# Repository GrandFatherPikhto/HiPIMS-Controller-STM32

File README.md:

# HiPiMS-Controller-STM32-v099

Плата управления HiPIMS: STM32F103C8 (U4) + Cyclone 10 LP 10CL006YE144 (IC1) с конфигурационным флешем
W25Q128JVS (U5).

Обозначения в этом файле — по схеме после переаннотации 16.11.2026.

## Что делает плата

* FPGA формирует сигналы управления: два силовых канала HP (по два плеча A/B, разъёмы J10/J11) и 12 логических
  каналов CH (J8/J9).
* STM32 — интерфейс оператора (LCD 1602 по I²C, энкодер с кнопкой), UART наружу и обмен с FPGA по SPI1.
* Все выходы и входы FPGA к разъёмам проходят через 74HC14 (U6–U13, питание 3.3 В). Каждый сигнал проходит два
  инвертора подряд, то есть уровень не инвертируется.

## Плата

* 4 слоя, 1.6 мм, около 115 × 94 мм.
* Зона GND_ALL на всех четырёх слоях, отдельных земель нет.
* Четыре крепёжных отверстия M3 (Ø 3.2 мм), межосевое 100.43 × 76.32 мм.

## Питание

Вход — **+5 В на J1** (JST VH, 1 = +5 В, 2 = GND). Защиты от переполюсовки нет: разъём полярный.

```text
J1 +5V_DIRTY ─ C9 100 мкФ ─ FB4 ─ +5V ─┬─ U2 AMS1117-3.3 ─ +3V3_DIRTY ─ FB1 ─ +3V3 ─┬─ FB10 ─ VCCIO FPGA
                                       │                                           ├─ FB6 ─ VDD MCU
                                       │                                           ├─ FB5 ─ VDDA MCU
                                       │                                           ├─ R26 2.2 Ом ─ флеш U5
                                       │                                           └─ R19 2.2 Ом ─ генератор Y3
                                       ├─ U1 AMS1117-1.2 ─ +1V2_DIRTY ─ FB2 ─ +1V2 ─┬─ FB7 ─ VCCINT
                                       │                                           └─ FB8 ─ VCCD_PLL
                                       ├─ U3 LM317 (R3 = R4 = 240 Ом) ─ +2V5_DIRTY ─ FB3 ─ +2V5 ─ FB9 ─ VCCA
                                       ├─ J5 (LCD), J6 (энкодер)
                                       └─ светодиод D6
```

* На входе AMS1117 — 10 мкФ + 100 нФ у вывода 3 (U1: C2/C6, U2: C1/C5).
* На выходе AMS1117 — тантал 47 мкФ (C3, C4); он даёт ESR, нужный для их устойчивости.
* У LM317 стоят D3 (выход → вход) и D4 (ADJ → выход) — штатная защита при разряде конденсаторов.
* Светодиоды питания: D6 синий (+5V), D1 зелёный (+3V3), D5 оранжевый (+2V5), D2 белый (+1V2) — про D2 см.
  «На проверку».

## Разъёмы

| Разъём | Тип | Назначение |
| --- | --- | --- |
| J1 | JST VH 2P | вход +5 В |
| J2 | штырь 1×2 | перемычка BOOT0 (STM32) |
| J3 | штырь 1×5 | SWD (STM32) |
| J4 | JST XH 4P | UART: 1 GND, 2 TX, 3 GND, 4 RX (через 330 Ом) |
| J5 | JST XH 4P | LCD 1602 (I²C): 1 GND, 2 +5V, 3 SDA (PB7), 4 SCL (PB6) |
| J6 | JST XH 5P | энкодер: 1 +5V, 2 A (PA0), 3 B (PA1), 4 кнопка (PA2), 5 GND |
| J7 | IDC 2×5 | JTAG FPGA (USB-Blaster) |
| J8 | IDC 2×6 | CH_OUT 0–5 на чётных выводах, нечётные — GND |
| J9 | IDC 2×6 | CH_OUT 6–11 на чётных выводах, нечётные — GND |
| J10 | IDC 2×6 | HP-канал 0 (плечи A/B) |
| J11 | IDC 2×6 | HP-канал 1 (плечи A/B) |

### HP-каналы (J10, J11)

| Вывод | Сигнал |
| --- | --- |
| 2 / 8 | CTL плеча A / B (выход) |
| 4 / 10 | RST плеча A / B (выход) |
| 6 / 12 | FLT плеча A / B (вход) |
| нечётные | GND |

* Стыкуются кабелем IDC 2×6 с J1 платы **HP-ISO-Channel-v099** (гальваническая развязка, дальше 5-вольтовая
  логика на HP-Channel / HP-Power). Логика на этом разъёме — 3.3 В.
* **CTL и RST** подтянуты к GND (2.2 кОм на входе 74HC14). Пока FPGA не сконфигурирована, на выходах «0»:
  ключ закрыт, драйвер в сбросе.
* **FLT** подтянут к GND (10 кОм, R48–R51). «0» = авария; снятый кабель тоже читается как авария. Это совпадает с
  fail-safe low у ISO7720F на HP-ISO-Channel.

### CH-каналы (J8, J9)

Двенадцать выходов FPGA через 74HC14. На входах буферов подтяжки 2.2 кОм к GND, поэтому во время конфигурации
FPGA на выходах «0».

## STM32 (U4)

* Кварцы: Y2 8 МГц (HSE, 12 пФ), Y1 32.768 кГц (LSE, 6.8 пФ).
* SPI1 к FPGA: PA4 CS_N (подтяжка 10 кОм вверх), PA5 SCK, PA6 MISO, PA7 MOSI; PB0 — IRQ от FPGA.
* I²C (LCD): PB6 SCL, PB7 SDA. Выводы 5-вольтовые (FT), подтяжки модуля LCD к +5 В допустимы.
* Энкодер: PA0, PA1, PA2. Подтяжек на плате нет — нужны внутренние подтяжки МК или подтяжки на модуле энкодера.
  См. «На проверку».
* Кнопка сброса SW1 (через 100 Ом на NRST).

## FPGA (IC1)

* Тактовая частота — генератор Y3 (корпус 3225), выход через 33 Ом. Вывод ST подтянут к питанию (1 кОм),
  питание генератора через 2.2 Ом.
* Конфигурация с флеша U5 — см. «Прошивка».

## На проверку

1. **D2 (белый, +1V2) не загорится.** Прямое напряжение белого светодиода около 3 В, а шина 1.2 В. Даже красному
   (≈1.8 В) не хватит. Если индикатор 1.2 В нужен — питать светодиод от +3V3 через транзистор, ключом от +1V2;
   иначе убрать D2 и R2.
2. **Энкодер на J6 — принято как есть.** Модуль энкодера с подтяжками питается +5 В, сигналы идут на PA0–PA2,
   которые у STM32F103 не 5-вольтовые (не FT). Ток через защитные диоды около 0.1–0.2 мА (10 кОм к 5 В), такая
   связка на практике работает. Строго по даташиту это выход за диапазон входа. Если когда-нибудь понадобится
   чисто — питать J6.1 от +3V3 или перенести сигналы на FT-выводы (PB…).
3. **Y3: значение в схеме — SG-7050CAN** (корпус 7.0 × 5.0 мм), а стоит генератор 3225. Исправить Value и
   Datasheet на реальный партномер, чтобы в BOM не ушёл чужой корпус. Предупреждение о фильтре футпринта после
   этого можно игнорировать.
4. **TCK подтянут 4.7 кОм** (R15), Intel советует 1 кОм — если JTAG сбоит.
5. **Площадка CL_NCONFIG** для прошивки флеша клипсой — при следующей доработке (см. «Прошивка»).
6. **На первой плате** осциллографом: +5V у входа AMS1117 и их выходы при включении и при подключении горячего
   источника. Затухающий выброс на 1–2 периода — норма. Долгий звон лечится резистором 0.5–1 Ом последовательно
   с одним из 10 мкФ.

## Прошивка

### STM32 (U4)

Основной путь — **SWD, разъём J3**:

| J3 | Цепь |
| --- | --- |
| 1 | +3V3 |
| 2 | SWDIO (PA13) |
| 3 | SWCLK (PA14) |
| 4 | NRST |
| 5 | GND |

* NRST выведен на разъём → можно подключаться с удержанием сброса (connect under reset), даже если прошивка
  отключила SWD.
* Если плата питается сама, вывод 3.3V программатора на J3.1 не подключать (у клонов ST-Link это выход). Хватает
  GND, SWDIO, SWCLK, NRST.

Запасной путь — **системный загрузчик по UART, разъём J4** (1 GND, 2 TX, 3 GND, 4 RX; линии через 330 Ом):

* BOOT0 подтянут к GND (R7 10 кОм), перемычка **J2** подаёт на него VDD. BOOT1 (PB2) — 10 кОм на GND.
* Перемычка J2 снята → старт из флеша; установлена → старт из системного загрузчика.

### FPGA: загрузка .sof по JTAG (без флеша)

Разъём **J7**, распиновка USB-Blaster: 1 TCK, 2 GND, 3 TDO, 4 VCC (+3V3), 5 TMS, 9 TDI, 10 GND (6–8 не
подключены). Загрузка в саму FPGA, флеш не участвует; пропадает при снятии питания.

TCK подтянут к GND 4.7 кОм (R15). Intel рекомендует 1 кОм; если JTAG сбоит на длинном кабеле — поменять R15
на 1 кОм.

### FPGA: конфигурация с флеша

Схема конфигурации — **AS ×1, стандартный POR, 3.3 В**: MSEL[2:0] = 010 (MSEL1 на VCCA, MSEL0/MSEL2 на GND),
nCE на GND, nCONFIG/nSTATUS/CONF_DONE подтянуты 10 кОм к +3V3_VCCIO. Шина AS напрямую к U5; WP и HOLD флеша
в «1».

**Флеш — Winbond, а не Intel EPCS/EPCQ.** Последствия:

1. **Галка Disable EPCS/EPCQ ID check — обязательна.** File → Convert Programming Files → **Advanced…** →
   **Disable EPCS/EPCQ ID check**. Галка записывается в сам файл прошивки и выключает проверку ID, которую
   **FPGA делает при загрузке с флеша**. Без неё Cyclone может не загрузиться с W25Q даже при правильно
   записанных данных. Ставить при генерации **и .jic, и .rpd**.
   Для `quartus_cpf` из командной строки то же самое — строка `PGMIO_IGNORE_EPCS_ID_CHECK=1` в `quartus.ini`.
2. **Целевое устройство при генерации — EPCQ128A** (или EPCS128): W25Q128JV в списке Quartus нет.
3. **Запись .jic через JTAG (J7).** Галка из п. 1 **не** отключает проверку ID, которую делает сам Quartus
   Programmer при записи. По отчётам W25Q128JV под EPCQ128A записывается, но это проверить на первой плате.

Проверка на первой плате:

1. Сгенерировать .jic под EPCQ128A с галкой из п. 1.
2. Записать через JTAG.
3. Снять и вернуть питание.
4. Убедиться, что CONF_DONE поднялся.

### FPGA: запасной путь — флеш напрямую клипсой

Если Quartus Programmer не возьмёт флеш, U5 пишется внешним SPI-программатором.

* **Клипса SOIC-8 208 mil** прямо на U5 (корпус 5.3 мм).
* **FPGA держать в сбросе:** CL_NCONFIG в «0» на всё время записи, тогда FPGA не выходит на шину AS. Отдельной
  площадки сейчас нет — только подтяжка R22. При доработке платы стоит добавить площадку CL_NCONFIG рядом с GND.
  (Поведение шины AS при nCONFIG = 0 и nCE = GND — сверить с Cyclone 10 LP Handbook, раздел AS-программирования.)
* **Питание — от платы**, VCC программатора не подключать: иначе через R26 (2.2 Ом) он кормит всю шину +3V3
  вместе с FPGA.
* **Логика программатора — 3.3 В.** Дешёвый CH341A «из коробки» даёт 5 В на SPI — нужна доработка на 3.3 В или
  другой программатор (FT2232H, Raspberry Pi, Bus Pirate).
* **Файл — .rpd**, а не .jic: Convert Programming Files, EPCQ128A, Active Serial, **с галкой Disable EPCS/EPCQ ID
  check**. Писать с адреса 0 (flashrom, ch341prog). В .rpd биты уже в порядке AS.
* После записи отпустить CL_NCONFIG или передёрнуть питание → CONF_DONE должен подняться.

### Источники

* [Cyclone 10 LP Handbook — MSEL Pin Settings](https://www.intel.com/content/www/us/en/docs/programmable/683777/current/msel-pin-settings.html)
* [AN 1013: Using Generic QSPI Flash — Disable Flash ID Check](https://www.intel.com/content/www/us/en/docs/programmable/855235/current/disable-flash-id-check.html)
* [Intel KB: When should the "Disable EPCS/EPCQ ID check" option be enabled](https://community.altera.com/kb/knowledge-base/when-should-the-%C2%93disable-epcsepcq-id-check%C2%94-option-be-enabled-in-the-convert-pro/340830)
* [Intel forum — W25Q128JVSIQ: which flash for .jic](https://community.altera.com/discussions/fpga-device/w25q128jvsiq-which-flash-for-jic-file/337276)
* [Intel forum — Cyclone 10 LP boot issue with W25Q128JVSIM](https://community.altera.com/discussions/quartus-prime/cyclone-10-lp-boot-up-issue-for-winbond-flash-w25q128jvsim-tr/313210)

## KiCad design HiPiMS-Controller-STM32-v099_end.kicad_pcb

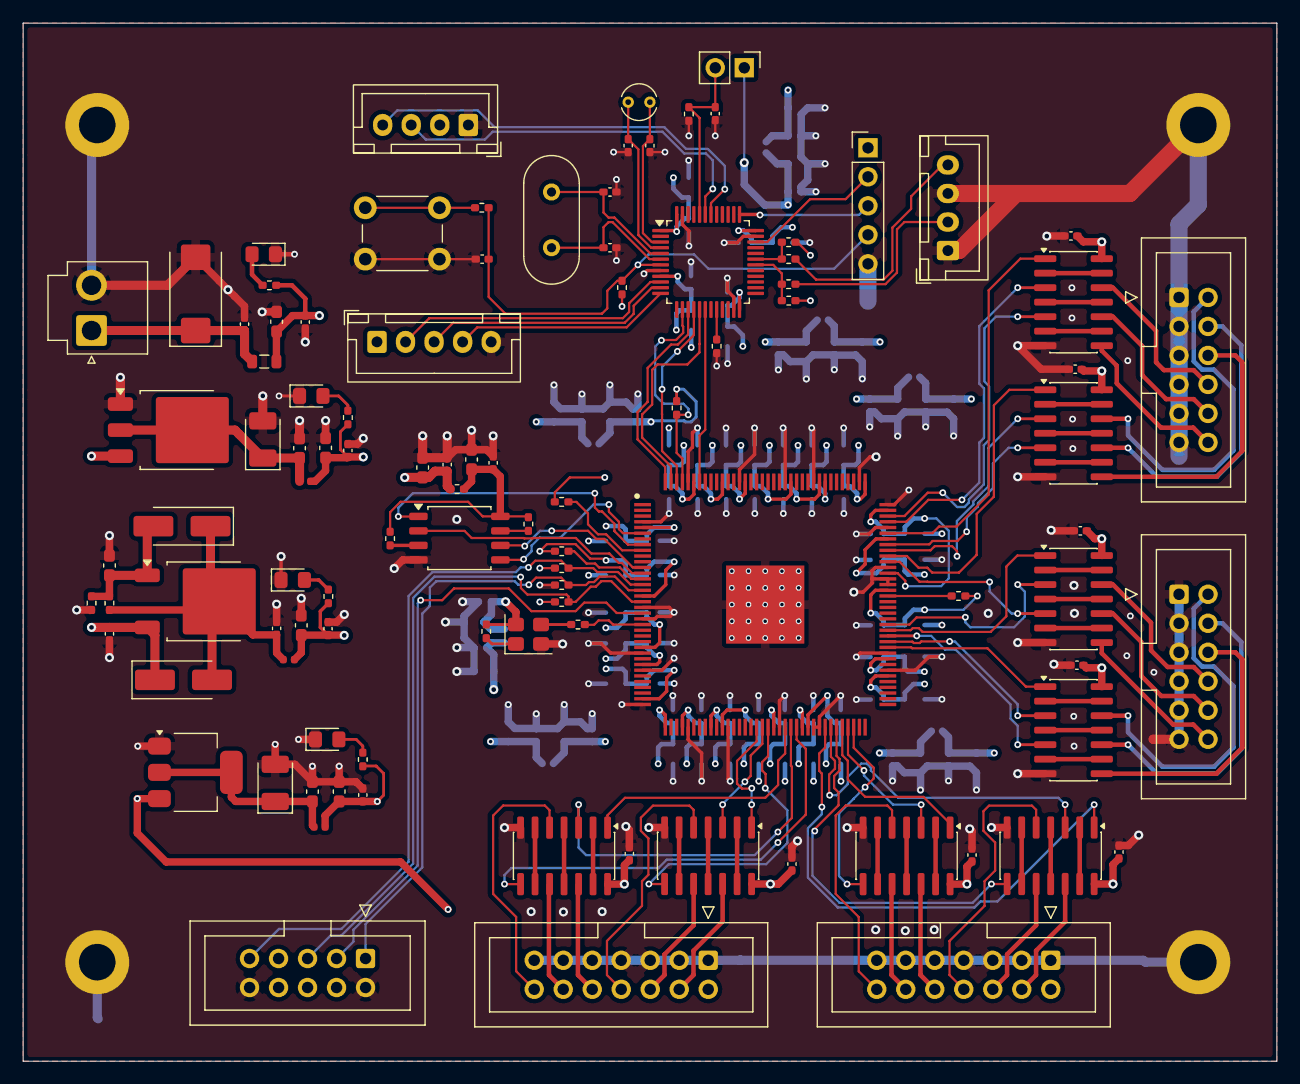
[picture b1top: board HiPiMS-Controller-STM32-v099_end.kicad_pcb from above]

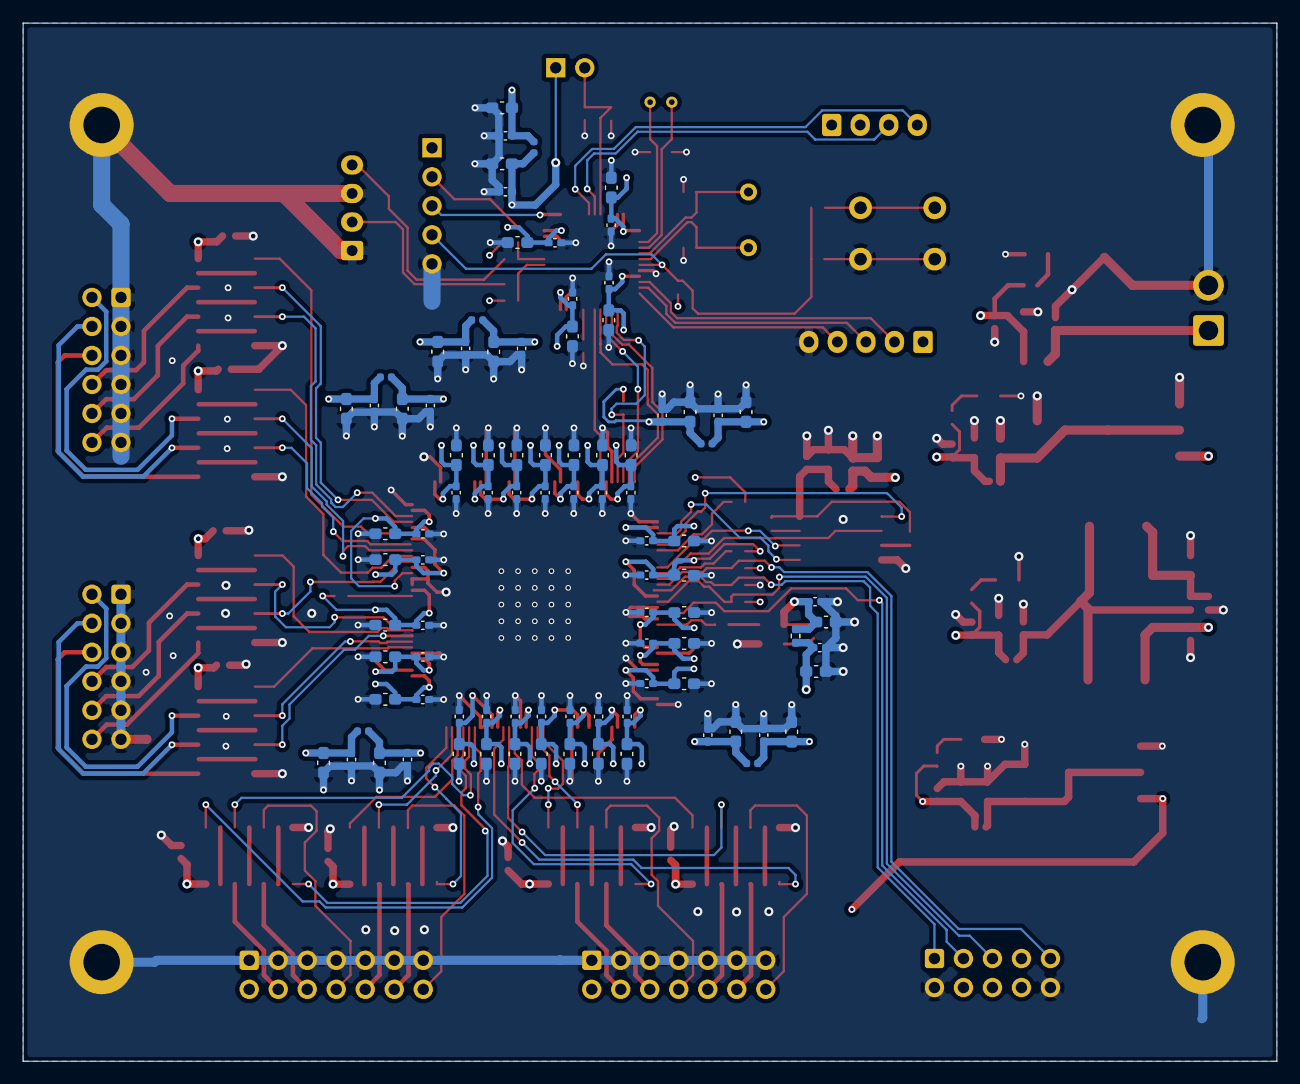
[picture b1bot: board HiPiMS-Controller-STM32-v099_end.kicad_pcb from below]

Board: 4 copper layers, 109.8 x 90.9 mm, 195 parts (91 on the bottom side), 134 nets.

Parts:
C1, C2: TAJB476K010UNJ; CP_EIA-3528-12_Kemet-T_HandSolder
C3, C4, C5, C6, C13, C15, C18, C19, C28, C29, C32, C33, C40, C41, C42, C43, C88, C89, C90, C91, C104, C105, C108, C109: 1 uF; C_0603_1608Metric_Pad1.08x0.95mm_HandSolder
C7, C8, C10, C11, C12, C16, C17, C22, C23, C24, C27, C30, C31, C36, C37, C38, C39, C44, C45, C46, C47, C48, C49, C50, C51, C52, C53, C54, C55, C56, C57, C58, C59, C72, C73, C74, C75, C76, C77, C78, C79, C96, C97, C98, C99, C100, C101, C102, C103, C106, C107, C110, C111: 100 nF; C_0402_1005Metric_Pad0.74x0.62mm_HandSolder
C9: TAJD107K016RNJ; CP_EIA-7343-20_Kemet-V_HandSolder
C14: 10 uF; C_0603_1608Metric_Pad1.08x0.95mm_HandSolder
C20, C25: 12 pF; C_0402_1005Metric_Pad0.74x0.62mm_HandSolder
C21, C26: 6.8 pF; C_0402_1005Metric_Pad0.74x0.62mm_HandSolder
C34, C35: 1uF; C_0603_1608Metric_Pad1.08x0.95mm_HandSolder
C60, C61, C62, C63, C64, C65, C66, C67, C68, C69, C70, C71, C80, C81, C82, C83, C84, C85, C86, C87, C92, C93, C94, C95: 4.7 uF; C_0603_1608Metric_Pad1.08x0.95mm_HandSolder
C112, C113, C114, C115, C116, C117, C118, C119: C; C_0402_1005Metric_Pad0.74x0.62mm_HandSolder
D1: LED Green; LED_0805_2012Metric_Pad1.15x1.40mm_HandSolder
D2: LED White; LED_0805_2012Metric_Pad1.15x1.40mm_HandSolder
D3, D4: 1N4001-SMA; D_SMA_Handsoldering
D5: LED Orange; LED_0805_2012Metric_Pad1.15x1.40mm_HandSolder
D6: LED Blue; LED_0805_2012Metric_Pad1.15x1.40mm_HandSolder
FB1, FB2, FB3, FB5, FB6, FB7, FB8, FB9, FB10: BLM15PD121SN1D; L_0402_1005Metric
FB4: BLM21PG121SN1D; L_0805_2012Metric
H1, H2, H3, H4: MountingHole_Pad; MountingHole_3.2mm_M3_DIN965_Pad
IC1: 10CL006YE144C8G; QFP50P2200X2200X165-145N
J1: P5V Input; JST_VH_B2P-VH-B_1x02_P3.96mm_Vertical
J2: Boot; PinHeader_1x02_P2.54mm_Vertical
J3: SWD; PinHeader_1x05_P2.54mm_Vertical
J4: USART; JST_XH_B4B-XH-A_1x04_P2.50mm_Vertical
J5: LCD1602; JST_XH_B4B-XH-A_1x04_P2.50mm_Vertical
J6: Rotary Encoder; JST_XH_B5B-XH-A_1x05_P2.50mm_Vertical
J7: CL_JTAG; IDC-Header_2x05_P2.54mm_Vertical
J8: Conn Channels 01; IDC-Header_2x06_P2.54mm_Vertical
J9: Conn Channels 02; IDC-Header_2x06_P2.54mm_Vertical
J10: Conn HP 01; IDC-Header_2x07_P2.54mm_Vertical
J11: Conn HP 02; IDC-Header_2x07_P2.54mm_Vertical
R1, R11, R12: 330; R_0402_1005Metric_Pad0.72x0.64mm_HandSolder
R2: 51; R_0402_1005Metric_Pad0.72x0.64mm_HandSolder
R3, R4: 240; R_0402_1005Metric_Pad0.72x0.64mm_HandSolder
R5: 220; R_0402_1005Metric_Pad0.72x0.64mm_HandSolder
R6: 470; R_0402_1005Metric_Pad0.72x0.64mm_HandSolder
R7, R8, R9, R13, R14, R20, R21, R22, R25: 10K; R_0402_1005Metric_Pad0.72x0.64mm_HandSolder
R10: 100; R_0402_1005Metric_Pad0.72x0.64mm_HandSolder
R15, R23, R24: 4.7K; R_0402_1005Metric_Pad0.72x0.64mm_HandSolder
R16, R18, R19, R26: 2R2; R_0402_1005Metric_Pad0.72x0.64mm_HandSolder
R17: 1K; R_0402_1005Metric_Pad0.72x0.64mm_HandSolder
R27: 33; R_0402_1005Metric_Pad0.72x0.64mm_HandSolder
SW1: SW_Push; SW_PUSH_6mm
U1: AMS1117CD-3.3; TO-252-3_TabPin2
U2: AMS1117-1.2; SOT-223-3_TabPin2
U3: LM317_TO-252; TO-252-2
U4: STM32F103C8Tx; LQFP-48_7x7mm_P0.5mm
U5: W25Q128JVS; SOIC-8_5.3x5.3mm_P1.27mm
U6, U7, U8, U9, U10, U11, U12, U13: 74HC14D; SOIC-14_3.9x8.7mm_P1.27mm
Y1: 8MHz; Crystal_HC49-4H_Vertical
Y2: 32.768KHz; Crystal_C38-LF_D3.0mm_L8.0mm_Vertical
Y3: SG-7050CAN; Crystal_SMD_3225-4Pin_3.2x2.5mm

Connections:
+1V2: C6.1, C8.1, C40.1, C41.1, C56.1, C57.1, FB2.2, FB7.1, FB8.1, R2.2
+1V2_DIRTY: C2.1, C4.1, FB2.1, U2.2 (VO)
+2V5: C13.1, C16.1, C42.1, C58.1, FB3.2, FB9.1, R5.2
+2V5_DIRTY: C11.1, D3.2 (A), D4.1 (K), FB3.1, R4.1, U3.2 (VO)
+3V3: C5.1, C7.1, C18.1, C19.1, C23.1, C24.1, C43.1, C59.1, C104.1, C105.1, C106.1, C107.1, C112.1, C113.1, C114.1, C115.1, C116.1, C117.1, C118.1, C119.1, FB1.2, FB5.1, FB6.1, FB10.1, J3.1, J7.4, R1.2, R19.1, R26.1, U6.14 (VCC), U7.14 (VCC), U8.14 (VCC), U9.14 (VCC), U10.14 (VCC), U11.14 (VCC), U12.14 (VCC), U13.14 (VCC)
+3V3_DIRTY: C1.1, C3.1, FB1.1, U1.2 (VO)
+5V: C10.2, C15.1, C17.1, D3.1 (K), FB4.2, J5.2, J6.1, J10.2, J11.2, R6.2, U1.3 (VI), U2.3 (VI), U3.3 (VI)
+5V_DIRTY: C9.1, C12.1, FB4.1, J1.1
/Connector/CH0: IC1.83 (IO_46), U6.1
/Connector/CH1: IC1.84 (IO_47), U6.3
/Connector/CH2: IC1.85 (IO_48), U6.5
/Connector/CH3: IC1.86 (IO_49), U7.1
/Connector/CH4: IC1.87 (IO_50), U7.3
/Connector/CH5: IC1.98 (IO_51), U7.5
/Connector/CH6: IC1.99 (IO_52), U8.1
/Connector/CH7: IC1.100 (IO_53), U8.3
/Connector/CH8: IC1.101 (IO_54), U8.5
/Connector/CH9: IC1.103 (IO_55), U9.1
/Connector/CH10: IC1.105 (IO_56), U9.3
/Connector/CH11: IC1.106 (IO_57), U9.5
/Connector/CH_OUT_0: J8.2, U6.12
/Connector/CH_OUT_1: J8.4, U6.10
/Connector/CH_OUT_2: J8.6, U6.8
/Connector/CH_OUT_3: J8.8, U7.12
/Connector/CH_OUT_4: J8.10, U7.10
/Connector/CH_OUT_5: J8.12, U7.8
/Connector/CH_OUT_6: J9.2, U8.12
/Connector/CH_OUT_7: J9.4, U8.10
/Connector/CH_OUT_8: J9.6, U8.8
/Connector/CH_OUT_9: J9.8, U9.12
/Connector/CH_OUT_10: J9.10, U9.10
/Connector/CH_OUT_11: J9.12, U9.8
/Connector/HP.0.A.CTL: IC1.53 (IO_26), U10.1
/Connector/HP.0.A.FLT: IC1.55 (IO_28), U10.8
/Connector/HP.0.A.IN.FLT: J10.8, U10.5
/Connector/HP.0.A.OUT.CTL: J10.4, U10.12
/Connector/HP.0.A.OUT.RST: J10.6, U10.10
/Connector/HP.0.A.RST: IC1.54 (IO_27), U10.3
/Connector/HP.0.B.CTL: IC1.58 (IO_29), U11.1
/Connector/HP.0.B.FLT: IC1.60 (IO_31), U11.8
/Connector/HP.0.B.IN.FLT: J10.14, U11.5
/Connector/HP.0.B.OUT.CTL: J10.10, U11.12
/Connector/HP.0.B.OUT.RST: J10.12, U11.10
/Connector/HP.0.B.RST: IC1.59 (IO_30), U11.3
/Connector/HP.1.A.CTL: IC1.65 (IO_32), U12.1
/Connector/HP.1.A.FLT: IC1.67 (IO_34), U12.8
/Connector/HP.1.A.IN.FLT: J11.8, U12.5
/Connector/HP.1.A.OUT.CTL: J11.4, U12.12
/Connector/HP.1.A.OUT.RST: J11.6, U12.10
/Connector/HP.1.A.RST: IC1.66 (IO_33), U12.3
/Connector/HP.1.B.CTL: IC1.68 (IO_35), U13.1
/Connector/HP.1.B.FLT: IC1.70 (IO_37), U13.8
/Connector/HP.1.B.IN.FLT: J11.14, U13.5
/Connector/HP.1.B.OUT.CTL: J11.10, U13.12
/Connector/HP.1.B.OUT.RST: J11.12, U13.10
/Connector/HP.1.B.RST: IC1.69 (IO_36), U13.3
/FPGA/+1V2_VCCD_PLL: C89.1, C92.1, C93.1, C97.1, C100.1, C101.1, FB8.2, IC1.37 (VCCD_PLL1), IC1.109 (VCCD_PLL2)
/FPGA/+1V2_VCCINT: C72.1, C73.1, C74.1, C75.1, C76.1, C77.1, C78.1, C79.1, C80.1, C81.1, C82.1, C83.1, C84.1, C85.1, C86.1, C87.1, C88.1, C96.1, FB7.2, IC1.5 (VCCINT_1), IC1.29 (VCCINT_2), IC1.45 (VCCINT_3), IC1.61 (VCCINT_4), IC1.78 (VCCINT_5), IC1.102 (VCCINT_6), IC1.116 (VCCINT_7), IC1.134 (VCCINT_8)
/FPGA/+2V5_VCCA: C90.1, C94.1, C95.1, C98.1, C102.1, C103.1, FB9.2, IC1.35 (VCCA1), IC1.96 (MSEL1), IC1.107 (VCCA2)
/FPGA/+3V3_FLASH: C109.1, C111.2, R16.2, R18.2, R26.2, U5.8 (VCC)
/FPGA/+3V3_OSCILL: C108.1, C110.2, R17.1, R19.2, Y3.4 (VCC)
/FPGA/+3V3_VCCIO: C44.1, C45.1, C46.1, C47.1, C48.1, C49.1, C50.1, C51.1, C52.1, C53.1, C54.1, C55.1, C60.1, C61.1, C62.1, C63.1, C64.1, C65.1, C66.1, C67.1, C68.1, C69.1, C70.1, C71.1, C91.1, C99.1, FB10.2, IC1.17 (VCCIO1), IC1.26 (VCCIO2), IC1.40 (VCCIO3_1), IC1.47 (VCCIO3_2), IC1.56 (VCCIO4_1), IC1.62 (VCCIO4_2), IC1.81 (VCCIO5), IC1.93 (VCCIO6), IC1.117 (VCCIO7_1), IC1.122 (VCCIO7_2), IC1.130 (VCCIO8_1), IC1.139 (VCCIO8_2), R20.2, R21.2, R22.2, R23.2, R24.2, R25.2
/FPGA/CL_ASDO: IC1.6 (IO_4), U5.5 (DI/IO_{0})
/FPGA/CL_CLK_0: R27.1, Y3.3 (OUT)
/FPGA/CL_CLK_0_IN: IC1.22 (CLK0), R27.2
/FPGA/CL_CLK_ON: R17.2, Y3.1 (~ST)
/FPGA/CL_CONFIG_DONE: IC1.92 (CONF_DONE), R20.1
/FPGA/CL_DATA0: IC1.13 (IO_10), U5.2 (DO/IO_{1})
/FPGA/CL_DCLK: IC1.12 (IO_9), U5.6 (CLK)
/FPGA/CL_NCONFIG: IC1.14 (NCONFIG), R22.1
/FPGA/CL_NCSO: IC1.8 (IO_6), U5.1 (~CS)
/FPGA/CL_NSTATUS: IC1.9 (NSTATUS), R21.1
/FPGA/CL_TCK: IC1.16 (TCK), J7.1, R15.1
/FPGA/CL_TDI: IC1.15 (TDI), J7.9, R24.1
/FPGA/CL_TDO: IC1.20 (TDO), J7.3
/FPGA/CL_TMS: IC1.18 (TMS), J7.5, R23.1
/FPGA/FL_HOLD: R16.1, U5.7 (~HOLD/~RESET/IO_{3})
/FPGA/FL_WP: R18.1, U5.3 (~WP/IO_{2})
/FPGA/SPI1.CS_N: IC1.141 (IO_78), R25.1, U4.14 (PA4)
/FPGA/SPI1.IRQ: IC1.138 (IO_77), U4.18 (PB0)
/FPGA/SPI1.MISO: IC1.142 (IO_79), U4.16 (PA6)
/FPGA/SPI1.MOSI: IC1.143 (IO_80), U4.17 (PA7)
/FPGA/SPI1.SCK: IC1.144 (IO_81), U4.15 (PA5)
/MCU/+3V3_VDD: C29.1, C31.1, C33.1, C34.1, C35.1, C37.1, C38.1, C39.1, FB6.2, J2.1, R9.2, R13.2, R14.2, U4.1 (VBAT), U4.24 (VDD), U4.36 (VDD), U4.48 (VDD)
/MCU/+3V3_VDDA: C28.1, C30.1, C32.1, C36.1, FB5.2, U4.9 (VDDA)
/MCU/BOOT0: C22.1, J2.2, R7.2, U4.44 (BOOT0)
/MCU/BOOT1: R8.2, U4.20 (PB2)
/MCU/LCD_SCL: J5.4, U4.42 (PB6)
/MCU/LCD_SDA: J5.3, U4.43 (PB7)
/MCU/NRST: C27.1, J3.4, R9.1, R10.2, U4.7 (NRST)
/MCU/RENC_A: J6.2, U4.10 (PA0)
/MCU/RENC_B: J6.3, U4.11 (PA1)
/MCU/RENC_BUTTON: J6.4, U4.12 (PA2)
/MCU/RX: R12.1, R14.1, U4.31 (PA10)
/MCU/RX_OUT: J4.4, R12.2
/MCU/SWCLK: J3.3, U4.37 (PA14)
/MCU/SWDIO: J3.2, U4.34 (PA13)
/MCU/TX: R11.1, R13.1, U4.30 (PA9)
/MCU/TX_OUT: J4.2, R11.2
/MCU/XTAL_8M_IN: C25.1, U4.5 (PD0), Y1.2
/MCU/XTAL_8M_OUT: C20.1, U4.6 (PD1), Y1.1
/MCU/XTAL_RTC_IN: C26.1, U4.3 (PC14), Y2.2
/MCU/XTAL_RTC_OUT: C21.1, U4.4 (PC15), Y2.1
/Power/+1V2_LED: D2.2 (A), R2.1
/Power/+2V5_ADJ: C14.1, D4.2 (A), R3.1, R4.2, U3.1 (ADJ)
/Power/+2V5_LED: D5.2 (A), R5.1
/Power/+3V3_LED: D1.2 (A), R1.1
/Power/+5V_LED: D6.2 (A), R6.1
GND: C1.2, C2.2, C3.2, C4.2, C5.2, C6.2, C7.2, C8.2, C9.2, C10.1, C11.2, C12.2, C13.2, C14.2, C15.2, C16.2, C17.2, C18.2, C19.2, C20.2, C21.2, C22.2, C23.2, C24.2, C25.2, C26.2, C27.2, C28.2, C29.2, C30.2, C31.2, C32.2, C33.2, C34.2, C35.2, C36.2, C37.2, C38.2, C39.2, C40.2, C41.2, C42.2, C43.2, C44.2, C45.2, C46.2, C47.2, C48.2, C49.2, C50.2, C51.2, C52.2, C53.2, C54.2, C55.2, C56.2, C57.2, C58.2, C59.2, C60.2, C61.2, C62.2, C63.2, C64.2, C65.2, C66.2, C67.2, C68.2, C69.2, C70.2, C71.2, C72.2, C73.2, C74.2, C75.2, C76.2, C77.2, C78.2, C79.2, C80.2, C81.2, C82.2, C83.2, C84.2, C85.2, C86.2, C87.2, C88.2, C89.2, C90.2, C91.2, C92.2, C93.2, C94.2, C95.2, C96.2, C97.2, C98.2, C99.2, C100.2, C101.2, C102.2, C103.2, C104.2, C105.2, C106.2, C107.2, C108.2, C109.2, C110.1, C111.1, C112.2, C113.2, C114.2, C115.2, C116.2, C117.2, C118.2, C119.2, D1.1 (K), D2.1 (K), D5.1 (K), D6.1 (K), H1.1 (1_1), H2.1 (1_1), H3.1 (1_1), H4.1 (1_1), IC1.4 (GND_1), IC1.19 (GND_2), IC1.21 (NCE), IC1.27 (GND_3), IC1.30 (GND_4), IC1.36 (GNDA1), IC1.41 (GND_5), IC1.48 (GND_6), IC1.57 (GND_7), IC1.63 (GND_8), IC1.64 (GND_9), IC1.79 (GND_10), IC1.82 (GND_11), IC1.94 (MSEL0), IC1.95 (GND_12), IC1.97 (MSEL2), IC1.104 (GND_13), IC1.108 (GNDA2), IC1.110 (GND_14), IC1.118 (GND_15), IC1.123 (GND_16), IC1.131 (GND_17), IC1.140 (GND_18), IC1.145 (EP_(GND)), J1.2, J3.5, J4.1, J4.3, J5.1, J6.5, J7.2, J7.10, J8.1, J8.3, J8.5, J8.7, J8.9, J8.11, J9.1, J9.3, J9.5, J9.7, J9.9, J9.11, J10.1, J10.3, J10.5, J10.7, J10.9, J10.11, J10.13, J11.1, J11.3, J11.5, J11.7, J11.9, J11.11, J11.13, R3.2, R7.1, R8.1, R15.2, SW1.2, U1.1 (GND), U2.1 (GND), U4.8 (VSSA), U4.23 (VSS), U4.35 (VSS), U4.47 (VSS), U5.4 (GND), U6.7 (GND), U7.7 (GND), U8.7 (GND), U9.7 (GND), U10.7 (GND), U11.7 (GND), U12.7 (GND), U13.7 (GND), Y3.2 (GND)
unnamed: R10.1, SW1.1
unnamed: U6.6, U6.9
unnamed: U6.4, U6.11
unnamed: U6.2, U6.13
unnamed: U7.6, U7.9
unnamed: U7.4, U7.11
unnamed: U7.2, U7.13
unnamed: U8.6, U8.9
unnamed: U8.4, U8.11
unnamed: U8.2, U8.13
unnamed: U9.6, U9.9
unnamed: U9.4, U9.11
unnamed: U9.2, U9.13
unnamed: U10.6, U10.9
unnamed: U10.4, U10.11
unnamed: U10.2, U10.13
unnamed: U11.6, U11.9
unnamed: U11.4, U11.11
unnamed: U11.2, U11.13
unnamed: U12.6, U12.9
unnamed: U12.4, U12.11
unnamed: U12.2, U12.13
unnamed: U13.6, U13.9
unnamed: U13.4, U13.11
unnamed: U13.2, U13.13
